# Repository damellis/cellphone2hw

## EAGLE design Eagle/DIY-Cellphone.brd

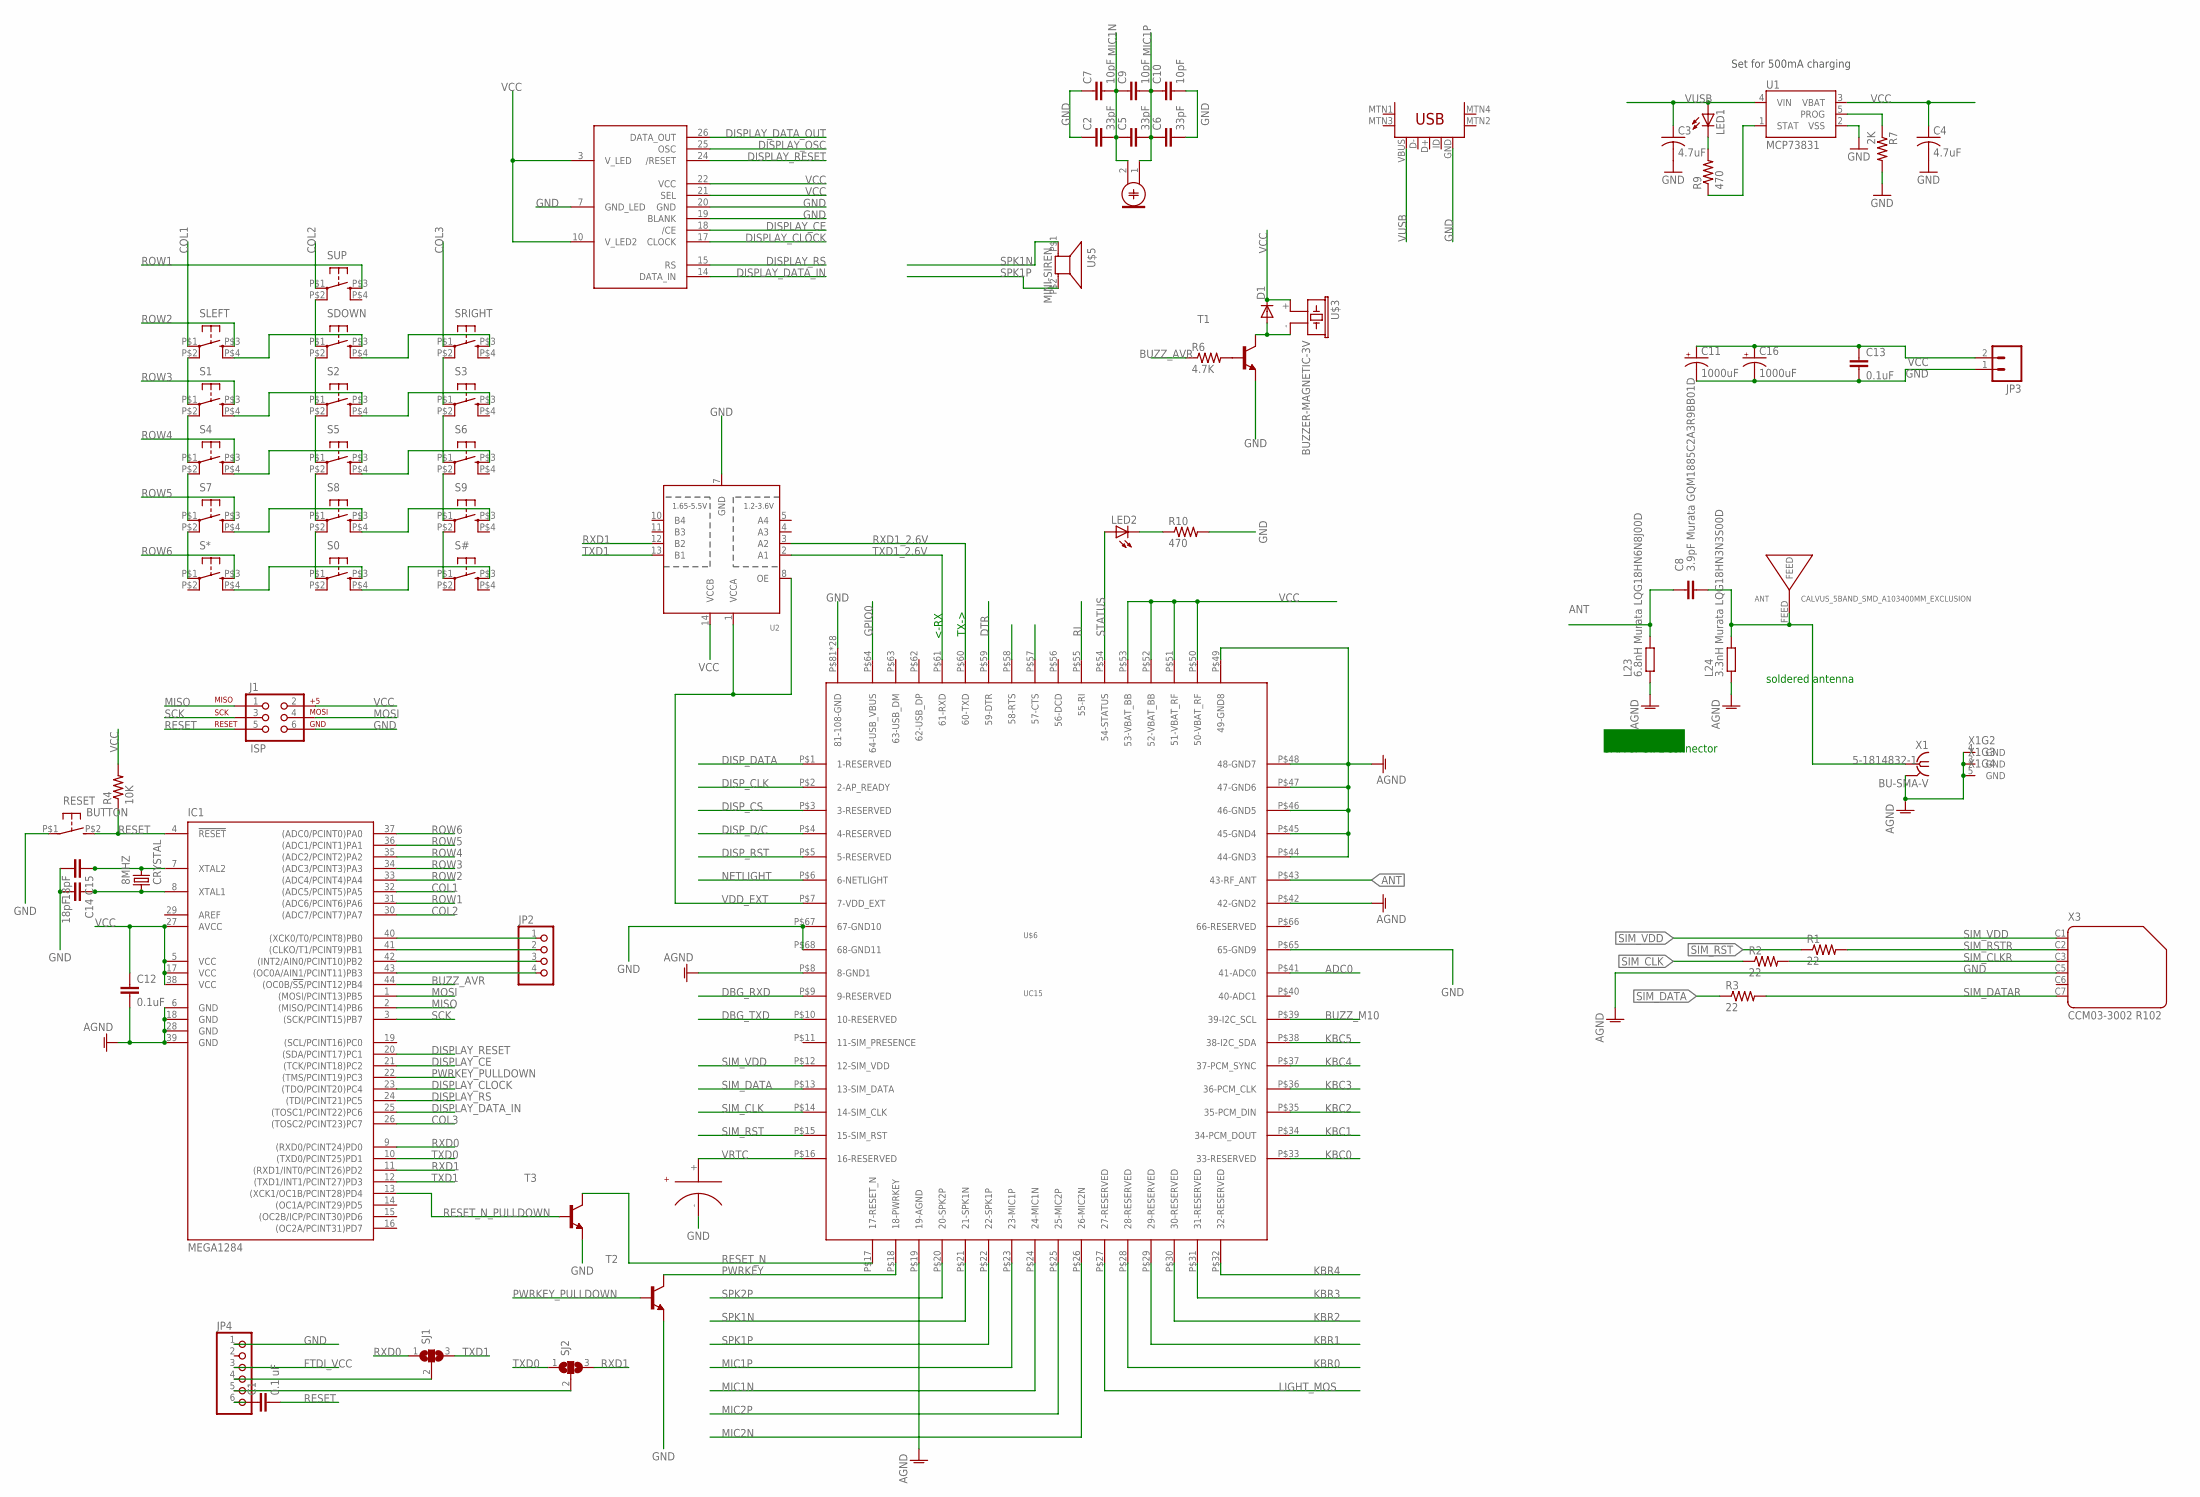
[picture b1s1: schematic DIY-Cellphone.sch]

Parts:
8MHZ: CRYSTAL; 2-SMD-5X3MM
ANT: CALVUS_5BAND_SMD_A103400MM_EXCLUSION; CALVUS_5BAND_SMD_A10340_0MM_EXCLUSION
C1: 0.1 uF; C1206
C2, C5, C6: 33pF; C1206
C3, C4: 4.7uF; C1206
C7, C9, C10: 10pF; C1206
C8: 3.9pF Murata GQM1885C2A3R9BB01D; C0603-ROUND
C11, C16: 1000uF; D/7343-31R
C12, C13: 0.1uF; C1206
C14, C15: 18pF; C1206
D1: DIODE-SOD123; SOD123
IC1: MEGA1284; TQFP44
J1: ISP; 2X3-NS
JP2: PINHD-1X4; 1X04
JP3: M02-JST-2MM-SMT; JST-2-SMD
JP4: PINHD-1X6/90; 1X06/90
L23: 6.8nH Murata LQG18HN6N8J00D; R0603-ROUND
L24: 3.3nH Murata LQG18HN3N3S00D; R0603-ROUND
LED1, LED2: LEDSMT1206; 1206
MIC: ELECTRET_MICROPHON-WM-64PC/64PK; WM-64PC/64PK
R1, R2, R3: 22; R1206
R4: 10K; R1206
R6: 4.7K; R1206
R7: 2K; R1206
R9, R10: 470; R1206
RESET: BUTTON; B3U-1000P
S0, S1, S2, S3, S4, S5, S6, S7, S8, S9: SWITCH-JLEAD; BUTTON_6MM_JLEAD
S#: SWITCH-JLEAD; BUTTON_6MM_JLEAD
S*: SWITCH-JLEAD; BUTTON_6MM_JLEAD
SDOWN: SWITCH-JLEAD; BUTTON_6MM_JLEAD
SJ1, SJ2: SJ2W; SJ_2
SLEFT: SWITCH-JLEAD; BUTTON_6MM_JLEAD
SRIGHT: SWITCH-JLEAD; BUTTON_6MM_JLEAD
SUP: SWITCH-JLEAD; BUTTON_6MM_JLEAD
T1, T2, T3: MMBT3904LT1-NPN-SOT23-BEC; SOT23-BEC
U1: MCP73831; SOT23-5
U2: TXB0104PWRSOIC14; SO14
U$1: USB-MINIB-5PIN; USB-MINIB
U$2: HCMS-[23]97X
U$3: BUZZER-MAGNETIC-3V; PUI-SMT-0540
U$4: SUPERCAPPAS; 414-VA5R
U$5: MINI-SIREN; SPEAKER-6.4MM
U$6: UC15
X1: BU-SMA-V
X3: CCM03-3002 R102; CON-AMPHENOL_C707_10M006_512_2

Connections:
ADC0: U$6.P$41 (41-ADC0)
ANT: C8.1, L23.2, U$6.P$43 (43-RF_ANT)
ANTENA: ANT.FEED, C8.2, L24.2, X1.1
AREF: IC1.29 (AREF)
BUZZ_AVR: IC1.44 ((OC0B/!SS!/PCINT12)PB4), R6.1
BUZZ_M10: U$6.P$39 (39-I2C_SCL)
COL1: IC1.32 ((ADC5/PCINT5)PA5), SLEFT.P$1
COL2: IC1.30 ((ADC7/PCINT7)PA7), SUP.P$1
COL3: IC1.26 ((TOSC2/PCINT23)PC7), SRIGHT.P$1
DBG_RXD: U$6.P$9 (9-RESERVED)
DBG_TXD: U$6.P$10 (10-RESERVED)
DISPLAY_CE: IC1.21 ((TCK/PCINT18)PC2), U$2.18 (/CE)
DISPLAY_CLOCK: IC1.23 ((TDO/PCINT20)PC4), U$2.17 (CLOCK)
DISPLAY_DATA_IN: IC1.25 ((TOSC1/PCINT22)PC6), U$2.14 (DATA_IN)
DISPLAY_DATA_OUT: U$2.26 (DATA_OUT)
DISPLAY_OSC: U$2.25 (OSC)
DISPLAY_RESET: IC1.20 ((SDA/PCINT17)PC1), U$2.24 (/RESET)
DISPLAY_RS: IC1.24 ((TDI/PCINT21)PC5), U$2.15 (RS)
DISP_CLK: U$6.P$2 (2-AP_READY)
DISP_CS: U$6.P$3 (3-RESERVED)
DISP_D/C: U$6.P$4 (4-RESERVED)
DISP_DATA: U$6.P$1 (1-RESERVED)
DISP_RST: U$6.P$5 (5-RESERVED)
DTR: U$6.P$59 (59-DTR)
FTDI_VCC: JP4.3
GND: C2.1, C3.2, C4.2, C6.2, C7.1, C10.2, C11.-, C12.2, C13.2, C14.2, C15.2, C16.-, IC1.6 (GND), IC1.18 (GND), IC1.28 (GND), IC1.39 (GND), J1.6, JP3.1 (2), JP4.1, L23.1, L24.1, R7.2, R10.2, RESET.P$1, T1.E, T2.E, T3.E, U1.2 (VSS), U2.7 (GND), U$1.GND, U$2.7 (GND_LED), U$2.19 (BLANK), U$2.20 (GND), U$4.-, U$6.P$8 (8-GND1), U$6.P$19 (19-AGND), U$6.P$42 (42-GND2), U$6.P$44 (44-GND3), U$6.P$45 (45-GND4), U$6.P$46 (46-GND5), U$6.P$47 (47-GND6), U$6.P$48 (48-GND7), U$6.P$49 (49-GND8), U$6.P$65 (65-GND9), U$6.P$67 (67-GND10), U$6.P$68 (68-GND11), U$6.P$81 (81-108-GND), U$6.P$82 (81-108-GND), U$6.P$83 (81-108-GND), U$6.P$84 (81-108-GND), U$6.P$85 (81-108-GND), U$6.P$86 (81-108-GND), U$6.P$87 (81-108-GND), U$6.P$88 (81-108-GND), U$6.P$89 (81-108-GND), U$6.P$90 (81-108-GND), U$6.P$91 (81-108-GND), U$6.P$92 (81-108-GND), U$6.P$93 (81-108-GND), U$6.P$94 (81-108-GND), U$6.P$95 (81-108-GND), U$6.P$96 (81-108-GND), U$6.P$97 (81-108-GND), U$6.P$98 (81-108-GND), U$6.P$99 (81-108-GND), U$6.P$100 (81-108-GND), U$6.P$101 (81-108-GND), U$6.P$102 (81-108-GND), U$6.P$103 (81-108-GND), U$6.P$104 (81-108-GND), U$6.P$105 (81-108-GND), U$6.P$106 (81-108-GND), U$6.P$107 (81-108-GND), U$6.P$108 (81-108-GND), X1.2 (GND), X1.3 (GND), X1.4 (GND), X1.5 (GND), X3.C5 (4)
GPIO0: U$6.P$64 (64-USB_VBUS)
KBC0: U$6.P$33 (33-RESERVED)
KBC1: U$6.P$34 (34-PCM_DOUT)
KBC2: U$6.P$35 (35-PCM_DIN)
KBC3: U$6.P$36 (36-PCM_CLK)
KBC4: U$6.P$37 (37-PCM_SYNC)
KBC5: U$6.P$38 (38-I2C_SDA)
KBR0: U$6.P$28 (28-RESERVED)
KBR1: U$6.P$29 (29-RESERVED)
KBR2: U$6.P$30 (30-RESERVED)
KBR3: U$6.P$31 (31-RESERVED)
KBR4: U$6.P$32 (32-RESERVED)
LIGHT_MOS: U$6.P$27 (27-RESERVED)
MIC1N: C2.2, C5.1, C7.2, C9.1, MIC.2, U$6.P$24 (24-MIC1N)
MIC1P: C5.2, C6.1, C9.2, C10.1, MIC.1, U$6.P$23 (23-MIC1P)
MIC2N: U$6.P$26 (26-MIC2N)
MIC2P: U$6.P$25 (25-MIC2P)
MISO: IC1.2 ((MISO/PCINT14)PB6), J1.1
MOSI: IC1.1 ((MOSI/PCINT13)PB5), J1.4
unnamed: D1.A, T1.C, U$3.- (2)
unnamed: C1.1, JP4.6
unnamed: R6.2, T1.B
unnamed: 8MHZ.P$2 (2), C15.1, IC1.7 (XTAL2)
unnamed: 8MHZ.P$1 (1), C14.1, IC1.8 (XTAL1)
unnamed: S1.P$1, SLEFT.P$2 (P1)
unnamed: S1.P$2 (P1), S4.P$1
unnamed: S4.P$2 (P1), S7.P$1
unnamed: JP4.4, SJ1.2
unnamed: SDOWN.P$1, SUP.P$2 (P1)
unnamed: S2.P$1, SDOWN.P$2 (P1)
unnamed: S2.P$2 (P1), S5.P$1
unnamed: S5.P$2 (P1), S8.P$1
unnamed: JP4.5, SJ2.2
unnamed: S3.P$1, SRIGHT.P$2 (P1)
unnamed: S3.P$2 (P1), S6.P$1
unnamed: S6.P$2 (P1), S9.P$1
unnamed: S0.P$4 (S1), S#.P$3 (S)
unnamed: S0.P$3 (S), S*.P$4 (S1)
unnamed: S7.P$4 (S1), S8.P$3 (S)
unnamed: S8.P$4 (S1), S9.P$3 (S)
unnamed: S4.P$4 (S1), S5.P$3 (S)
unnamed: S5.P$4 (S1), S6.P$3 (S)
unnamed: S1.P$4 (S1), S2.P$3 (S)
unnamed: S2.P$4 (S1), S3.P$3 (S)
unnamed: SDOWN.P$3 (S), SLEFT.P$4 (S1)
unnamed: SDOWN.P$4 (S1), SRIGHT.P$3 (S)
unnamed: S7.P$2 (P1), S*.P$1
unnamed: S0.P$1, S8.P$2 (P1)
unnamed: S9.P$2 (P1), S#.P$1
unnamed: R9.1, U1.1 (STAT)
unnamed: LED1.C, R9.2
unnamed: LED2.C, R10.1
unnamed: IC1.40 ((XCK0/T0/PCINT8)PB0), JP2.1
unnamed: IC1.41 ((CLKO/T1/PCINT9)PB1), JP2.2
unnamed: IC1.42 ((INT2/AIN0/PCINT10)PB2), JP2.3
unnamed: IC1.43 ((OC0A/AIN1/PCINT11)PB3), JP2.4
NETLIGHT: U$6.P$6 (6-NETLIGHT)
PROG: R7.1, U1.5 (PROG)
PWRKEY: T2.C, U$6.P$18 (18-PWRKEY)
PWRKEY_PULLDOWN: IC1.22 ((TMS/PCINT19)PC3), T2.B
RESET: C1.2, IC1.4 (!RESET), J1.5, R4.1, RESET.P$2 (S)
RESET_N: T3.C, U$6.P$17 (17-RESET_N)
RESET_N_PULLDOWN: IC1.13 ((XCK1/OC1B/PCINT28)PD4), T3.B
RI: U$6.P$55 (55-RI)
ROW1: IC1.31 ((ADC6/PCINT6)PA6), SUP.P$3 (S)
ROW2: IC1.33 ((ADC4/PCINT4)PA4), SLEFT.P$3 (S)
ROW3: IC1.34 ((ADC3/PCINT3)PA3), S1.P$3 (S)
ROW4: IC1.35 ((ADC2/PCINT2)PA2), S4.P$3 (S)
ROW5: IC1.36 ((ADC1/PCINT1)PA1), S7.P$3 (S)
ROW6: IC1.37 ((ADC0/PCINT0)PA0), S*.P$3 (S)
RXD0: IC1.9 ((RXD0/PCINT24)PD0), SJ1.1
RXD1: IC1.11 ((RXD1/INT0/PCINT26)PD2), SJ2.3, U2.12 (B2)
RXD1_2.6V: U2.3 (A2), U$6.P$60 (60-TXD)
SCK: IC1.3 ((SCK/PCINT15)PB7), J1.3
SIM_CLK: R2.1, U$6.P$14 (14-SIM_CLK)
SIM_CLKR: R2.2, X3.C3 (3)
SIM_DATA: R3.1, U$6.P$13 (13-SIM_DATA)
SIM_DATAR: R3.2, X3.C7 (6)
SIM_RST: R1.1, U$6.P$15 (15-SIM_RST)
SIM_RSTR: R1.2, X3.C2 (2)
SIM_VDD: U$6.P$12 (12-SIM_VDD), X3.C1 (1)
SPK1N: U$5.P$1 (1), U$6.P$21 (21-SPK1N)
SPK1P: U$5.P$2 (2), U$6.P$22 (22-SPK1P)
SPK2P: U$6.P$20 (20-SPK2P)
STATUS: LED2.A, U$6.P$54 (54-STATUS)
TXD0: IC1.10 ((TXD0/PCINT25)PD1), SJ2.1
TXD1: IC1.12 ((TXD1/INT1/PCINT27)PD3), SJ1.3, U2.13 (B1)
TXD1_2.6V: U2.2 (A1), U$6.P$61 (61-RXD)
VCC: C4.1, C11.+, C12.1, C13.1, C16.+, D1.C, IC1.5 (VCC), IC1.17 (VCC), IC1.27 (AVCC), IC1.38 (VCC), J1.2, JP3.2 (1), R4.2, U1.3 (VBAT), U2.14 (VCCB), U$2.3 (V_LED), U$2.10 (V_LED2), U$2.21 (SEL), U$2.22 (VCC), U$3.+ (1), U$6.P$50 (50-VBAT_RF), U$6.P$51 (51-VBAT_RF), U$6.P$52 (52-VBAT_BB), U$6.P$53 (53-VBAT_BB)
VDD_EXT: U2.1 (VCCA), U2.8 (OE), U$6.P$7 (7-VDD_EXT)
VRTC: U$4.+, U$6.P$16 (16-RESERVED)
VUSB: C3.1, LED1.A, U1.4 (VIN), U$1.VBUS

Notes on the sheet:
soldered antenna
SMA or U.FL connector
TX->
<-RX
Set for 500mA charging

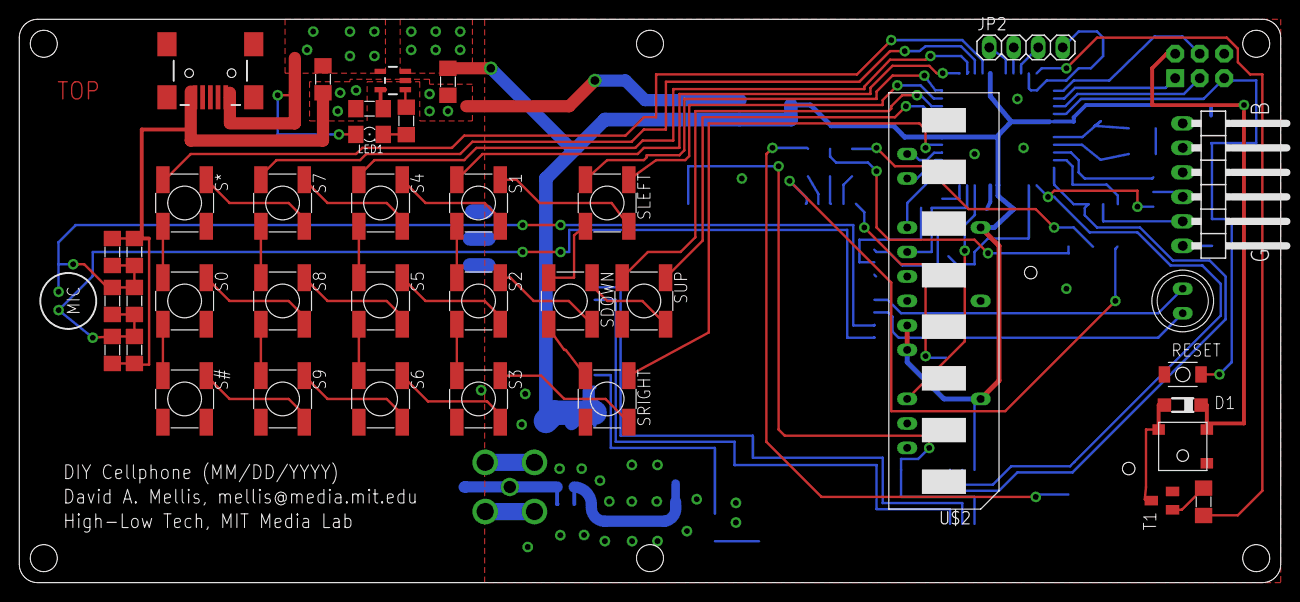
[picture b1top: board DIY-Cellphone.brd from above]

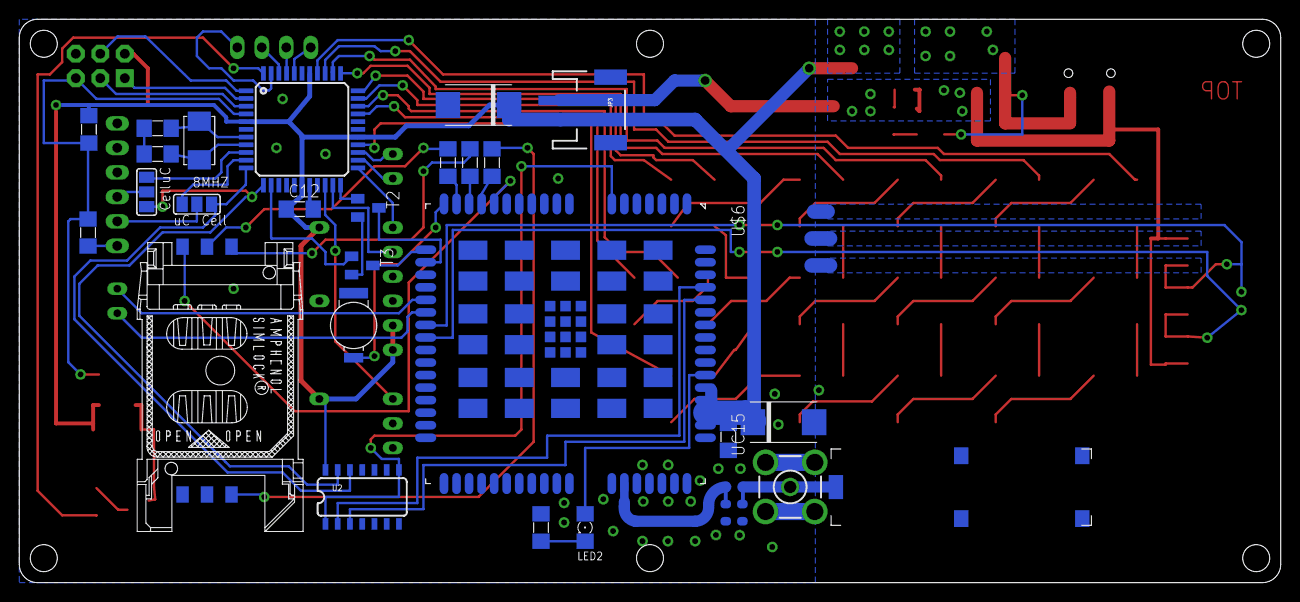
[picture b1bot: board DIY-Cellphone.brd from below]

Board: 2 copper layers, 130.8 x 58.4 mm, 69 parts (29 on the bottom side), 86 nets.

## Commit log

2012-12-12 First prototype of the second-generation DIY cellphone.
2012-12-12 Updating for new speaker, making shorter.
2012-12-13 Re-arranging after making shorter.
2012-12-13 Adding reset button.
2012-12-13 Made holes for screen bigger.
2012-12-13 New supercap.
2012-12-13 Updating BOM with new super-cap.
2012-12-13 Adding heat dissipation and LED on charging circuit.
2012-12-13 Use 2200 uF capacitor instead of two 1000 uF ones.
2012-12-13 Reverting to two caps. Labeling FTDI header colors.
2012-12-13 Moving capacitors (near the cellular module).
2012-12-13 Revert "Use 2200 uF capacitor instead of two 1000 uF ones."
    This reverts commit 187005bbbcca3f0aea18f2a290581fd565eadcb0.
2012-12-15 Add LED on M10 status pin.
2012-12-15 Break out additional microcontroller pins.
2012-12-15 Remove RTS/CTS connection on M10.
2012-12-17 Make mounting holes smaller and move inwards slightly.
2012-12-17 Add buzzer hole. Align buzzer / reset button / speaker. Move some wires.
2012-12-17 Adjust silk-screen.
2012-12-17 Add datasheet for buzzer.
2012-12-17 Generate new gerbers.
2013-01-03 Update pdf files of top and bottom.
2013-01-03 Add my gerber export cam file.
2013-01-03 Enlarge mounting holes and move closer to PCB edge.
2013-01-03 Update date in silk screen.
2013-01-04 Add value (100 ohms) to resistor on LED backlight for the display.
2013-01-04 Update BOM to include part numbers and prices for all electronics.
2013-01-04 Update date.
2013-01-04 Extend stop mask over VCC and GND traces on USB connector (issue #5).
2013-01-04 Add gerbers.
2013-01-07 Update pdf's (for 12/17/2012 version).
2013-01-07 Update top plywood case to PCB from 12/17/2012.
2013-01-07 Update case bottom for 12/17/2012 prototype.
2013-01-09 Redo case top (to fix double-outlines from "stroke to path").
2013-01-09 Update top and bottom veneer. Hide circuit layer in bottom plywood.
2013-01-09 Change stroke width of bottom veneer to match top veneer.
2013-01-10 Update hpgl and Corel Draw files for 12/17/2012 case.
2013-01-15 Update PDFs of Eagle files (board top and bottom, schematic).
2013-01-15 Update case SVG files for 1/4/2013 PCB (new screw holes).
2013-01-15 Change visible layers.
2013-03-04 Update BOM.
2013-03-04 Create footprint for HCMS-[23]79X.
2013-03-05 Routing.
2013-03-06 Route everything (not thoroughly verified yet).
2013-03-08 Add datasheet for Avago HCMS-39xx LED 5x7 display.
2013-03-14 Remove "top" label; update date in silkscreen, etc.
2013-03-14 Add gerbers for LED matrix variant (although BatchPCB didn't like them).
2013-03-19 Update hpgl and CDR plywood files (top and bottom) to latest design (new holes).
2013-03-19 Update veneer files: new flexure buttons, updated hpgl and CDR files.
2013-03-25 Enlarging holes in bottom veneer (Inkscape only so far) to fit nuts.
2013-04-04 Not sure what changed, to be honest. :)
2013-04-04 Add outlines and polarity indicators to component silkscreen (tPlace).
2013-04-18 Shrink holes back to old, smaller size and update date.
    The corners line up with the 12/17/2012 prototype but the center holes don't (they're moved to be in the middle of the corner holes).
2013-04-19 Adding gerbers for 2013-04-18.
2013-05-04 Update PDFs (top, bottom, and schematic).
2013-05-04 Update top (plywood) SVG for LED matrix.
2013-05-04 Shrink holes in top for smaller screws.
2013-05-04 Update bottom for LED matrix (and delete old layer in top).
2013-05-07 Align central screw holes with corner holes. Update CDR and hpgl files.
2013-05-08 Update veneer files for LED matrix.
2013-05-09 Expand holes in bottom veneer to accomodate nuts.
2013-05-09 Expand button and speakers holes to allow for misalignment in soldering.
2013-05-09 Replace little, per-LED holes with a bigger cutout for the whole LED matrix.
2013-05-16 Update PDFs of cellphone top and bottom.
2013-05-17 Link to M10 module on the Arduino store.
2013-05-21 Add male headers to BOM and add PDF of BOM.
2013-05-23 Update SVG files for smaller screws.
2013-05-23 Remove out-of-date HPGL and CDR files.
2013-05-29 Initial files for a CNC routed case.
2013-05-29 Update files for CNC routed case: bigger holes (for this PCB), merge outline.
2013-05-29 Thinner strokes.
2013-05-29 Expand speaker pocket and buttons holes.
2013-05-30 Remove duplicate path (hole for display).
2013-05-30 Add holes for the ISP header in the plywood (top and bottom).
2013-05-30 Add HPGL and coreldraw (CDR) files.
2013-05-31 Add dxf, partworks, and shopbot files for CNC case.
2013-06-05 Rip up most traces, remove buttons and display, start laying out components.
2013-06-08 Add ISP header to BOM. Update BOM PDF.
2013-06-12 Add outlines and polarity indicators to silkscreen.
    Like 8e50b8ee63d6100466716e3ad2a6bf83c7afc136
2013-06-12 Enlarge pads for reset button.
2013-06-12 Add updated gerber files.
2013-06-21 Update BOM for LED matrix variant.
2013-06-27 Add PDF of BOM.
2013-06-28 Add version of the top veneer with numbers.
    The -Text file has the numbers as editable text, the -Path file has it as a path, for export to the laser cutter.
2013-07-05 Expand button and speaker holes to allow for tolerance in soldering.
2013-07-05 Make all lines opaque.
2013-07-05 Update files for jumper wire from PB4 to buzzer.
    This is for driving the buzzer from the microcontroller instead of the GSM module (for newer GSM modules that don't support ring tones).
2013-07-06 Solder jumper to connect buzzer to GSM module or microcontroller (PB4).
2013-07-30 Solder jumper to connect buzzer to GSM module or microcontroller (PB4).
    Conflicts:
    Eagle/DIY-Cellphone.brd
    Eagle/DIY-Cellphone.sch
2013-07-30 Revert "Shrink holes back to old, smaller size and update date."
    This reverts commit 7fec822335ff7942d5890c8d80fcf110c2a2e6df.
2013-07-30 Enlarge pads for reset button.
    Conflicts:
    Eagle/cellphone.lbr
2013-07-31 Add "top" label to top copper layer and update date.
2013-07-31 Add updated gerbers.
2013-08-01 Update circuit board top and bottom PDFs.
2013-08-01 Import new circuit into top case, make room for buzzer solder jumper.
2013-08-01 Make all strokes 100% opaque.
2013-08-01 Make room in top plywood of case to accommodate FTDI breakout (issue #30).
2013-08-08 Add date and generate gerbers.
2013-08-08 Update PDFs.
2013-08-08 Update PDFs again, after ratsnest (polygon fill).
2013-08-08 New PDFs again.
2013-08-08 Update for new PCB (big holes and buzzer jumper).
2013-08-08 Update for new holes.
2013-08-08 Remove old top plywood files.
2013-08-08 Initial untested version of a CNC-milled solid wood case, with magnets.
2013-08-12 Remove old layer in top solid file and add toolpaths.
    The toolpath files are only for reference and might not work with your setup. In particular, this file assumes that the phone is being cut out of the end of a 324" piece of wood.
2013-08-12 Add top solid dxf file, too.
2013-08-13 Update bottom solid files (for CNC milling).
    Again, these should only be used with care. For example, the toolpath for the bottom is at x of 0, and places the phone in the middle of a 3" high stock (y).
2013-08-16 Remove more components, rearrange components.
2013-08-23 Not sure.
2013-08-23 Continuing to organize. Headers on side now, most components in place.
2013-08-26 Route some traces. Update PDFs.
2013-08-27 Route more. Move ISP header.
2013-08-28 Route power section.
2013-08-29 Route almost all remaining traces except gnd and pwrkey.
2013-09-25 Add CAM processor job and Gerbers for ordering from OSH Park.
2013-09-26 Add Eagle component for bigger speaker from CUI (Digi-Key #102-1543-ND).
2013-09-26 Add OSH Park gerber cam job and gerbers.
2013-10-07 Route remaining airwires. Replace FTDI footprint w/ one with no holes.
2013-10-07 Move board to the origin. Label some unused pins.
2013-10-10 Update silk screen labels, polygon isolate, etc.
2013-10-10 Remove Gerbers from other branch.
2013-10-10 Increase polygon width,
2013-10-10 Add gerber files.
2013-10-24 Add thermals and increase isolate on ground planes for easier soldering.
2013-10-28 Break out I2C and SPI pins.
2013-10-28 Break out power and ground.
2013-10-28 Move FTDI header to edge of board.
2013-10-28 Add LEDs for power and pin 13.
2013-10-29 Move speaker and mic to edge of board.
2013-10-29 Connect airwire.
2013-10-29 Add date.
2013-11-21 Add hpgl and CDR files for plywood top.
2013-11-23 Update top veneer CDR and hpgl files, and delete obsolete bottom ones.
2013-11-25 Add header pins for speaker and mic, and separate other speaker and mic pins.
2013-11-26 Move FTDI B and G labels, and via.
2013-11-26 Solder stop mask on USB power pins, labels on mic and speaker header pins.
2013-11-26 Update date and generate gerbers.
2014-03-04 Update solid case SVG files to 2013-08-08 PCB (larger holes and buzzer jumper).
2014-03-04 Update solid case files for different pocket heights (from LED matrix).
2014-03-04 Add pockets for magnets, as an alternative layer to the screw holes.
2014-03-24 Add groove for wire jumper (from buzzer to microcontroller) on old PCBs.
2014-03-24 Add DXF, PartWorks, and ShopBot files for CNC case (missing mic hole).
    Note: the toolpaths in these files are missing a hole for the microphone.
2014-03-28 Add CDR and .hpgl for bottom veneer with holes for countersinking nuts.
2014-08-18 Ignore Eagle backup files.
2014-08-18 Export M10 from .sch / .brd to cellphone.lbr
2014-08-18 Create UC15 footprint; replace M10 w/ UC15.
    Warning: this board won’t work! Note that many of the traces on the
    board now overlap the new pads on the UC15 (that aren’t on the M10).
2014-08-19 Connect buzzer directly to microcontroller.
    Remove solder jumper that allows it to go to the Quectel module, since
    the UC15 drops the buzzer pin.
2014-08-19 Re-route traces to avoid new UC15 pads.
    Warning: this board still won’t work, as it’s missing level shifters
    between the UC15 and the ATmega1284.
2014-08-19 Add TXB0104 level shifter.
2014-09-04 Move dowel holes to separate layer; add hole for jumper wire solder.
2014-09-05 Update PartWorks (.crv) files, add ShopBot (.sbp) files.
    Untested. Origin at bottom-left of parts. Includes holes for jumper wire solder and channel for jumper wire. No microphone hole. No dowel holes.
2014-09-09 Fix origin on ShopBot and PartWorks files.
    They were offset from the origin; this translates them to the origin.
2014-11-07 Add transistors and finish routing.
    PWRKEY and RESET_N now have transistors between UC15 module and
    ATmega1284.
2014-11-18 Connect fourth VCC pin and additional GND pins.
2015-04-01 Update Partworks and Shopbot files.
    Remove dowel holes, move top files closer to X origin, slow down top
    files (to 60/30 from 100/50 rates), make cutouts deeper on top files
    (0.27” instead of 0.26”), add some tabs and make tabs thicker.

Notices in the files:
parts and their libraries:
SparkFun-Connectors: Licensing: CC v3.0 Share-Alike You are welcome to use this library for commercial purposes.
SparkFun-DigitalIC: Licensing: Creative Commons ShareAlike 4.0 International - https://creativecommons.org/licenses/by-sa/4.0
